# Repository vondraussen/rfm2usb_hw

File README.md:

# RFM2USB Hardware
USB to RFM69 board made with Kicad. Uses a STM32L151 microcontroller.
Firmware repo is [here](https://github.com/vondraussen/rfm2usb).

## Schematic

## Board

# Tools
```bash
pip install pcbdraw
```

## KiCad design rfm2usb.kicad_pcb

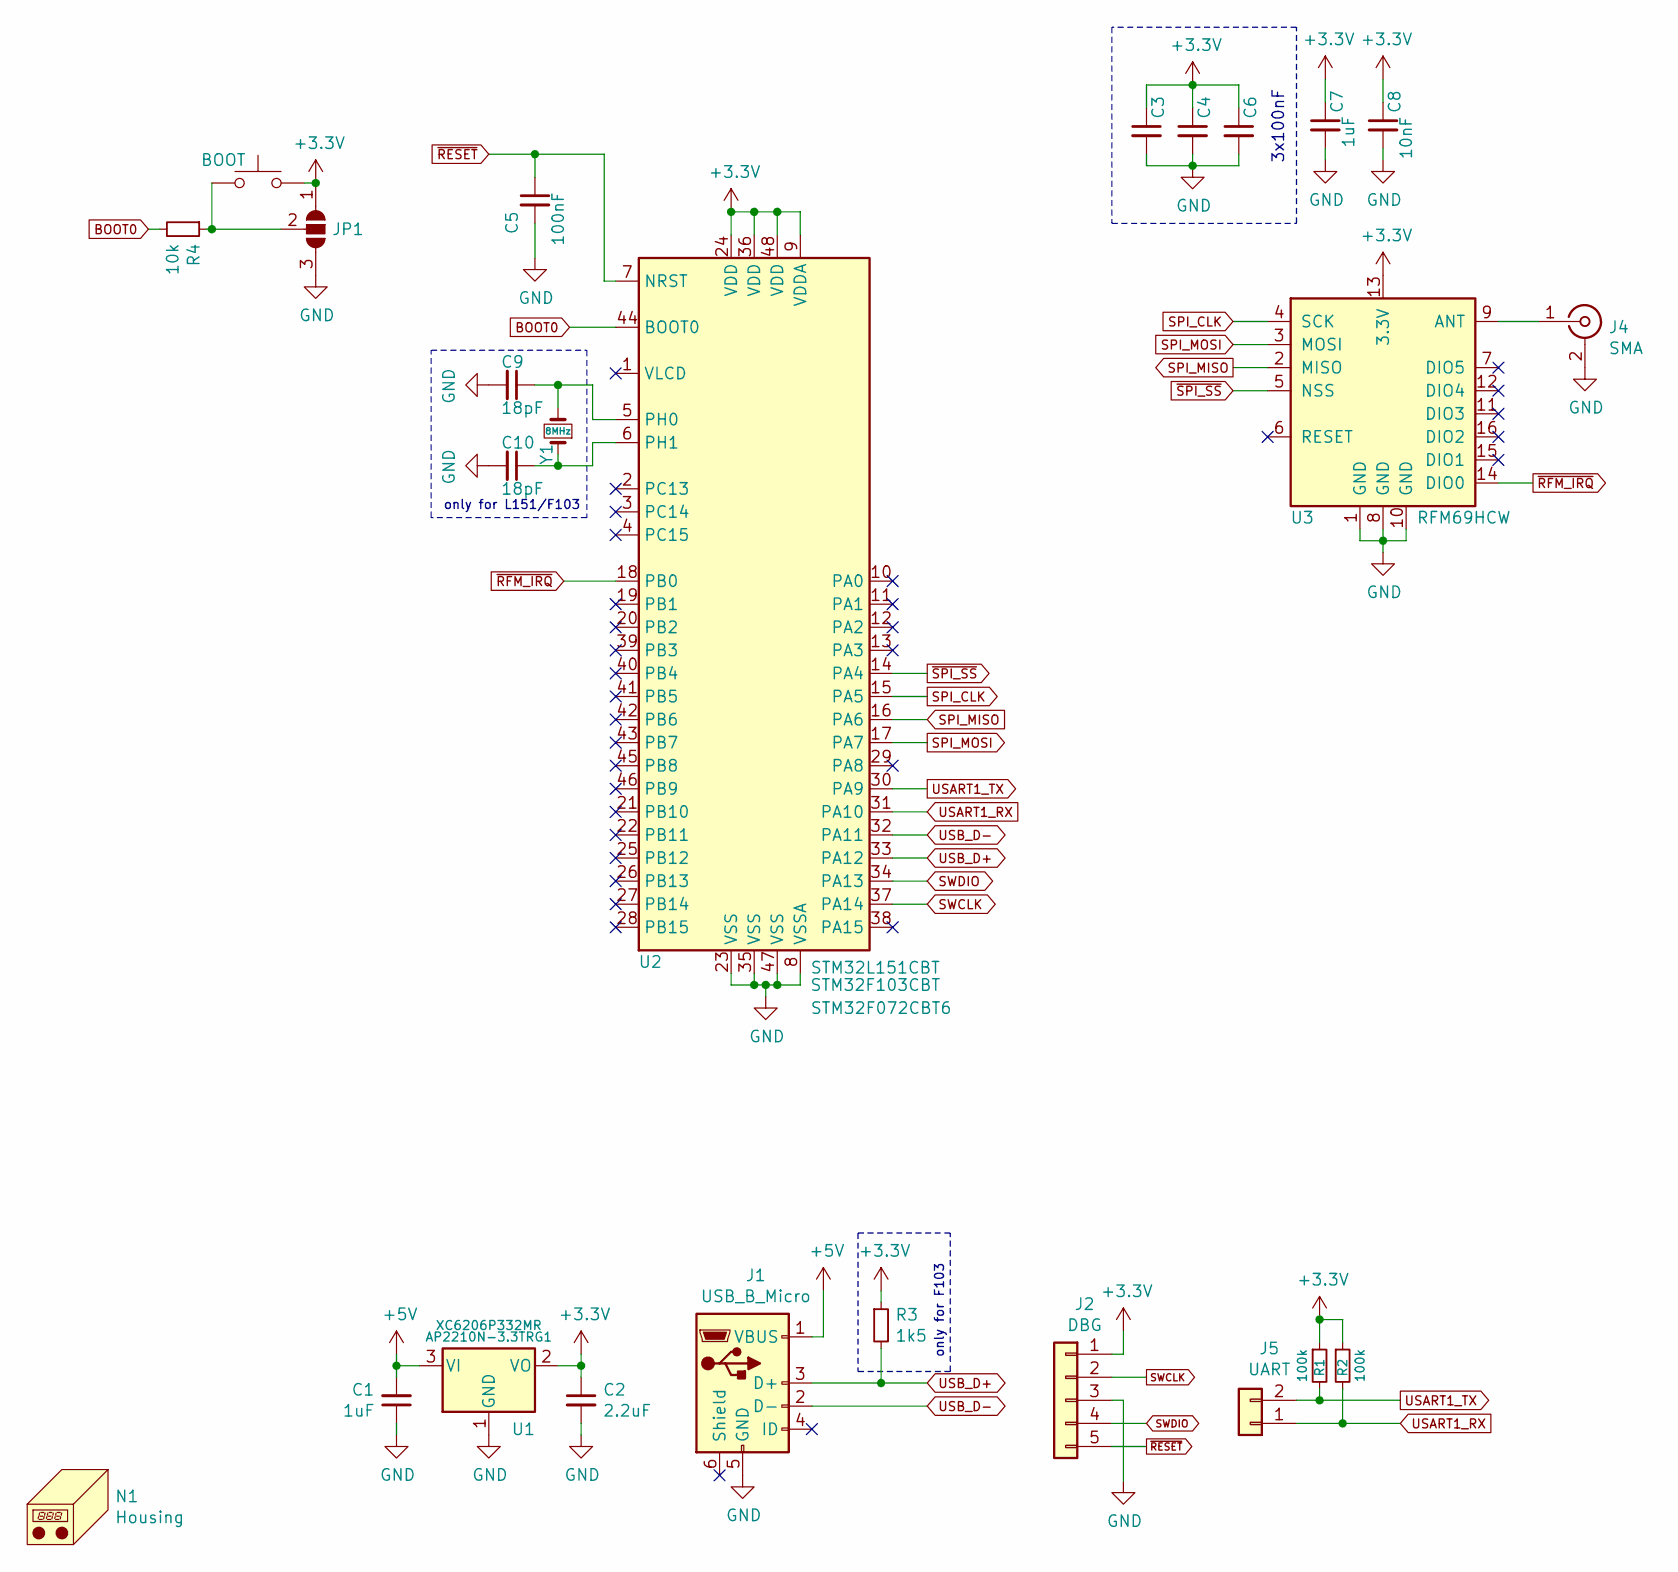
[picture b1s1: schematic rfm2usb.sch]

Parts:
BOOT1: BOOT; SW_Push_1P1T_NO_CK_KMR2; PART KMR241NG ULC LFS; Digikey CKN10285CT-ND‎
C1, C7: 1uF; C_0603_1608Metric
C2: 2.2uF; C_0603_1608Metric; Digikey 1276-1183-1-ND‎
C3, C4, C5, C6: 100nF; C_0603_1608Metric
C8: 10nF; C_0603_1608Metric
C9, C10: 18pF; C_0603_1608Metric; Digikey ‎1292-1494-1-ND‎
J1: USB_B_Micro; USB_Micro-B_Amphenol_10118194_Horizontal; Digikey ‎609-4618-1-ND‎
J2: DBG; PinHeader_1x05_P2.54mm_Vertical
J4: SMA; SMA_Molex_73251-1153_EdgeMount_Horizontal
J5: UART; PinHeader_1x02_P2.54mm_Vertical
JP1: SolderJumper_3_Open; SolderJumper-3_P1.3mm_Open_RoundedPad1.0x1.5mm_NumberLabels
N1: Housing; KiCad-Logo2_5mm_Copper
R1, R2: 100k; R_0603_1608Metric
R3: 1k5; R_0603_1608Metric
R4: 10k; R_0603_1608Metric
U1: AP2210N-3.3TRG1; SOT-23; Digikey AP2210N-3.3TRG1DICT-ND‎
U2: STM32L151CBT; LQFP-48_7x7mm_P0.5mm; Digikey 497-17516-1-ND‎
U3: RFM69HCW; HOPERF_RFM9XW_SMD
Y1: 8MHz; Crystal_SMD_3225-4Pin_3.2x2.5mm; Digikey ‎50-ECS-80-12-33Q-GN-CT-ND‎

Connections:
+3V3: BOOT1.2, C2.1, C3.1, C4.1, C6.1, C7.1, C8.1, J2.1, JP1.1 (A), R1.1, R2.1, R3.1, U1.2 (VO), U2.9 (VDDA), U2.24 (VDD), U2.36 (VDD), U2.48 (VDD), U3.13 (3.3V)
+5V: C1.2, J1.1 (VBUS), U1.3 (VI)
BOOT0: R4.2, U2.44 (BOOT0)
GND: C1.1, C2.2, C3.2, C4.2, C5.2, C6.2, C7.2, C8.2, C9.2, C10.2, J1.5 (GND), J2.3, J4.2 (Ext), JP1.3 (B), U1.1 (GND), U2.8 (VSSA), U2.23 (VSS), U2.35 (VSS), U2.47 (VSS), U3.1 (GND), U3.8 (GND), U3.10 (GND)
unnamed: BOOT1.1, JP1.2 (C), R4.1
unnamed: C9.1, U2.5 (PH0), Y1.2
unnamed: C10.1, U2.6 (PH1), Y1.1
unnamed: J4.1 (In), U3.9 (ANT)
SPI_CLK: U2.15 (PA5), U3.4 (SCK)
SPI_MISO: U2.16 (PA6), U3.2 (MISO)
SPI_MOSI: U2.17 (PA7), U3.3 (MOSI)
SWCLK: J2.2, U2.37 (PA14)
SWDIO: J2.4, U2.34 (PA13)
USART1_RX: J5.1, R2.2, U2.31 (PA10)
USART1_TX: J5.2, R1.2, U2.30 (PA9)
USB_D+: J1.3 (D+), R3.2, U2.33 (PA12)
USB_D-: J1.2 (D-), U2.32 (PA11)
~RESET: C5.1, J2.5, U2.7 (NRST)
~RFM_IRQ: U2.18 (PB0), U3.14 (DIO0)
~SPI_SS: U2.14 (PA4), U3.5 (NSS)

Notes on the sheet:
3x100nF
only for L151/F103
only for F103

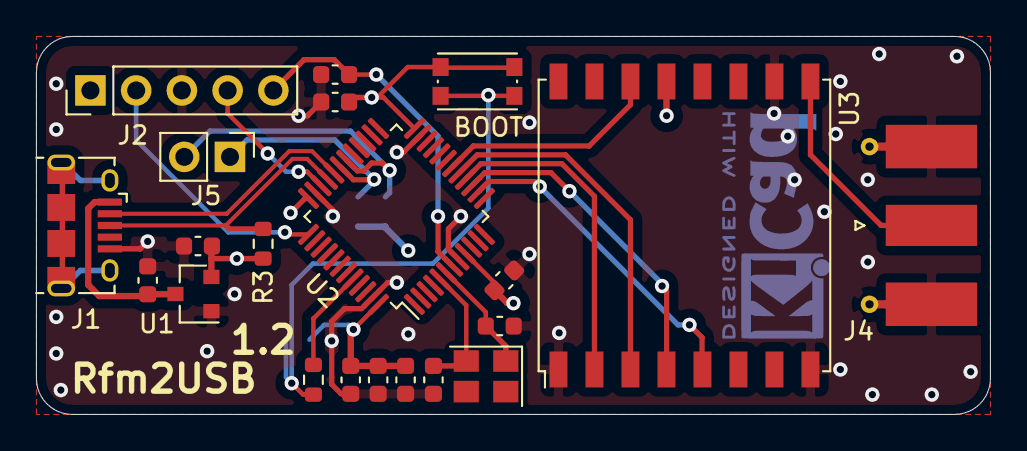
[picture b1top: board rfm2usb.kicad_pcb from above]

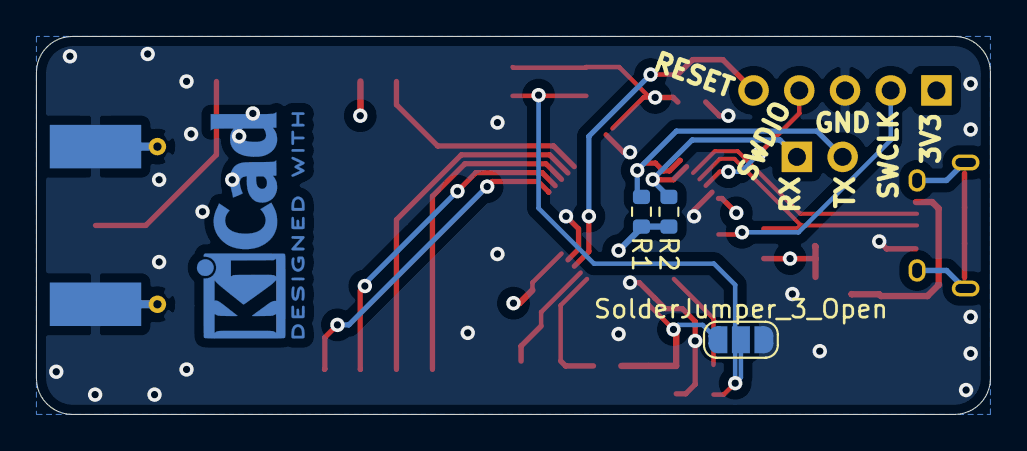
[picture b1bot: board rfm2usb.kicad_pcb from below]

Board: 4 copper layers, 53.0 x 21.0 mm, 25 parts (4 on the bottom side), 20 nets.

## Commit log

2021-02-18 init commit
2021-02-18 add docs kibot config
2021-02-18 add readme
2021-02-18 add gerber export action
2021-02-19 cleanup
2021-02-20 auto export
2021-03-06 change stm32 footprint
2021-03-06 fix clearance false pos
2021-09-11 use svg for board pics
2021-09-11 replace reset button with boot button this is more useful
